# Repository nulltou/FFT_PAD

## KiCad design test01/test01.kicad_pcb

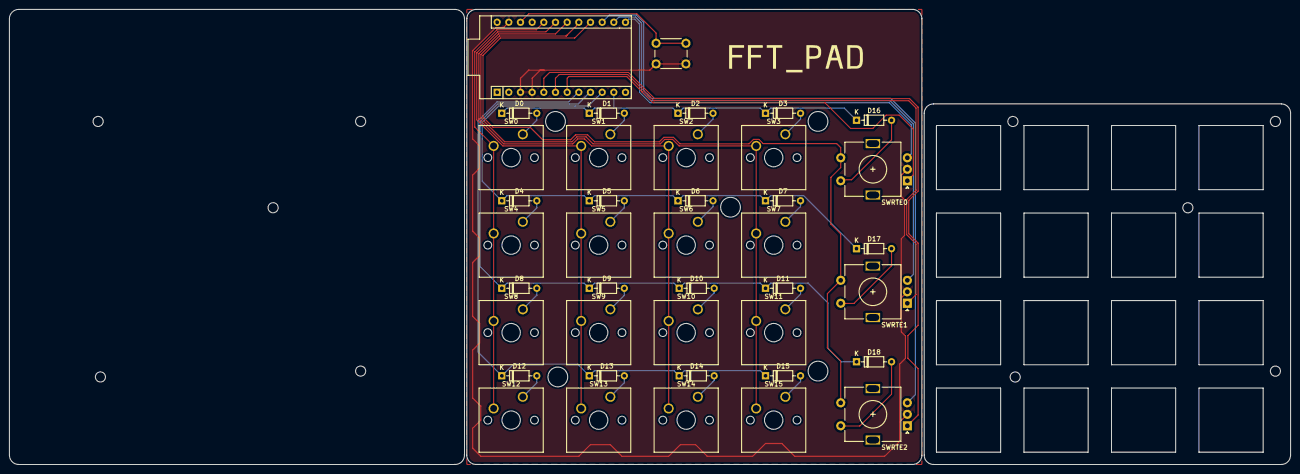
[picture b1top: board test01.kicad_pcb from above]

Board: 2 copper layers, 278.9 x 99.1 mm, 45 parts (0 on the bottom side), 36 nets.

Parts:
D0, D1, D2, D3, D4, D5, D6, D7, D8, D9, D10, D11, D12, D13, D14, D15, D16, D17, D18: 1N4148; D_DO-35_SOD27_P7.62mm_Horizontal
Ref**: Val**; M2_HOLE_v2
Ref**#2, Ref**#3, Ref**#4, Ref**#5: Val**; M2_HOLE_v2
SW0, SW1, SW2, SW3, SW4, SW5, SW6, SW7, SW8, SW9, SW10, SW11, SW12, SW13, SW14, SW15: SW_Push; SW_Cherry_MX_1.00u_PCB
SW19: SW_Push; SW_PUSH_6mm
SWRTE0, SWRTE1, SWRTE2: RotaryEncoder_Switch; RotaryEncoder_Alps_EC11E-Switch_Vertical_H20mm
Sparkfun_Pro_Micro1: Pro_Micro; Sparkfun_Pro_Micro

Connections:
GND: SW19.2, SWRTE0.C, SWRTE1.C, SWRTE2.C, Sparkfun_Pro_Micro1.3 (GND), Sparkfun_Pro_Micro1.4 (GND), Sparkfun_Pro_Micro1.23 (GND)
unnamed: D0.2 (A), SW0.1
unnamed: D1.2 (A), SW1.1
unnamed: D2.2 (A), SW2.1
unnamed: D3.2 (A), SW3.1
unnamed: D4.2 (A), SW4.1
unnamed: D5.2 (A), SW5.1
unnamed: D6.2 (A), SW6.1
unnamed: D7.2 (A), SW7.1
unnamed: D8.2 (A), SW8.1
unnamed: D9.2 (A), SW9.1
unnamed: D10.2 (A), SW10.1
unnamed: D11.2 (A), SW11.1
unnamed: D12.2 (A), SW12.1
unnamed: D13.2 (A), SW13.1
unnamed: D14.2 (A), SW14.1
unnamed: D15.2 (A), SW15.1
unnamed: D16.2 (A), SWRTE0.S2
unnamed: D17.2 (A), SWRTE1.S2
unnamed: D18.2 (A), SWRTE2.S2
RST: SW19.1, Sparkfun_Pro_Micro1.22 (RST)
RTE0: SWRTE0.B, Sparkfun_Pro_Micro1.13 (~D10/A10)
RTE1: SWRTE1.B, Sparkfun_Pro_Micro1.14 (D16)
RTE2: SWRTE2.B, Sparkfun_Pro_Micro1.15 (D14)
RTE3: SWRTE0.A, Sparkfun_Pro_Micro1.7 (D4/A6)
RTE4: SWRTE1.A, Sparkfun_Pro_Micro1.6 (~D3)
RTE5: SWRTE2.A, Sparkfun_Pro_Micro1.5 (D2)
col0: SW0.2, SW4.2, SW8.2, SW12.2, Sparkfun_Pro_Micro1.20 (D21/A3)
col1: SW1.2, SW5.2, SW9.2, SW13.2, Sparkfun_Pro_Micro1.19 (D20/A2)
col2: SW2.2, SW6.2, SW10.2, SW14.2, Sparkfun_Pro_Micro1.18 (D19/A1)
col3: SW3.2, SW7.2, SW11.2, SW15.2, Sparkfun_Pro_Micro1.17 (D18/A0)
col4: SWRTE0.S1, SWRTE1.S1, SWRTE2.S1, Sparkfun_Pro_Micro1.16 (D15)
row0: D0.1 (K), D1.1 (K), D2.1 (K), D3.1 (K), D16.1 (K), Sparkfun_Pro_Micro1.11 (D8/A8)
row1: D4.1 (K), D5.1 (K), D6.1 (K), D7.1 (K), D17.1 (K), Sparkfun_Pro_Micro1.10 (D7)
row2: D8.1 (K), D9.1 (K), D10.1 (K), D11.1 (K), D18.1 (K), Sparkfun_Pro_Micro1.9 (~D6/A7)
row3: D12.1 (K), D13.1 (K), D14.1 (K), D15.1 (K), Sparkfun_Pro_Micro1.8 (~D5)

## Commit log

2022-05-06 Kicad files
